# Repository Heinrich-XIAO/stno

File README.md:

# stno

stno is a one-handed steno keyboard with joysticks for my thumb. I wanted to make stno because I became obsessed with steno, didn't have an n-key roll over keyboard and i didnt want to keep arpegiating, and i wanted a one-handed keyboard like my other keyboards (all of them were too small for a steno layout). I wanted to use joysticks since i feel like holding two keys with one finger is awkward and wanted to minimize it, especially for the thumb.

## 🟩PCB

## 📐Schematic

## 📏CAD

## 📦BOM

| Name                 | Price (and Currency) | Link/source                                                                                | Notes                                                                                                                                                                                                                   |
|----------------------|----------------------|--------------------------------------------------------------------------------------------|-------------------------------------------------------------------------------------------------------------------------------------------------------------------------------------------------------------------------|
| Springs              | $13.49 CAD           | https://www.aliexpress.com/item/1005006171011050.html                                      | $4.52 after welcome deal                                                                                                                                                                                                |
| TTC Neptune Switches | $27.26 USD           | https://milktooth.com/products/neptune                                                     | $5.09 per pack $11.99 shipping                                                                                                                                                                                          |
| Arduino Nano ESP32   | $29.67 USD           | https://store-usa.arduino.cc/products/nano-esp32                                           |                                                                                                                                                                                                                         |
| Joysticks            | $21.67 CAD           | https://www.amazon.com/PS5-Hall-Effect-Joystick-Replacement-2-Pack/dp/B0DN8T9KJW           | $7.68 shipping + $13.99                                                                                                                                                                                                 |
| Thumbscrews          | $13.99 CAD           | https://www.amazon.ca/MECCANIXITY-Stainless-Thumbscrew-Appliances-Electronic/dp/B0F282TJ7D |                                                                                                                                                                                                                         |
| Nuts and Bolts       | $13.11 CAD           | https://www.amazon.ca/Walfront-Socket-Head-Button-Screws/dp/B0742DDLQ1                     | this is an assortment of screws but its still somehow cheaper than some non-assortements ive found. it also means hackclub won't have to pay for 10 dollars worth of bolts every time i need a different length of bolt |
| Keycaps              | $5.31 CAD            | https://www.aliexpress.com/item/1005008653485944.html                                      | 3 packs of ten $1.36 per pack                                                                                                                                                                                           |
| Heatset Inserts      | $4.79 CAD            | https://www.aliexpress.com/item/1005003582355741.html                                      | m3 4mm $1.39 after welcome deal                                                                                                                                                                                         |
| Hotswap Sockets      | $9.83 CAD            | https://www.aliexpress.com/item/1005003913466247.html                                      | $1.39 after welcome deal                                                                                                                                                                                                |
| PCB                  | $31.82 USD           | JLCPCB                                                                                     |                                                                                                                                                                                                                         

Total: $145.99 USD

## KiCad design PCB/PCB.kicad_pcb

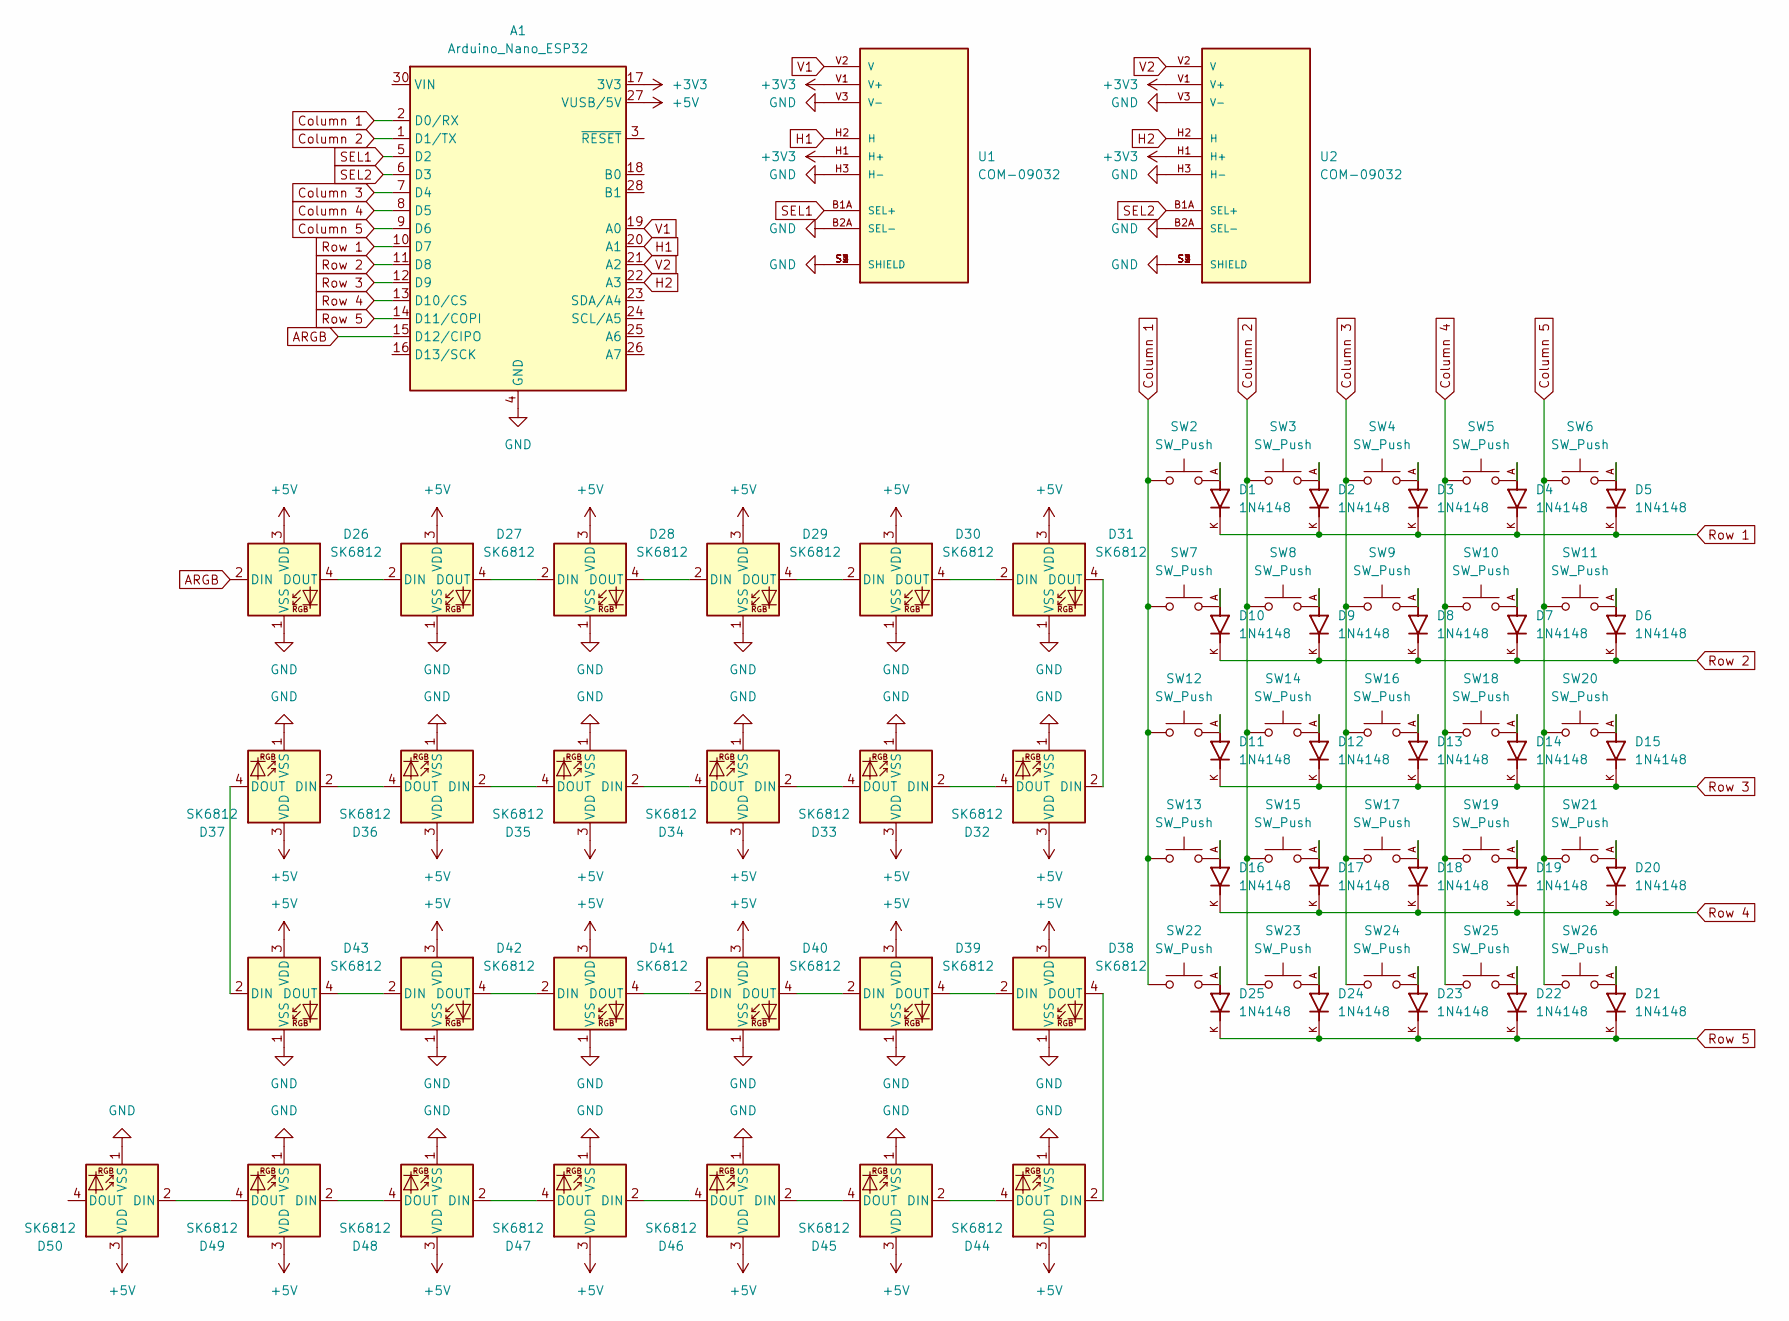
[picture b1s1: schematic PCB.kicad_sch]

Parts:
A1: Arduino_Nano_ESP32; Arduino_Nano
D1, D2, D3, D4, D5, D6, D7, D8, D9, D10, D11, D12, D13, D14, D15, D16, D17, D18, D19, D20, D21, D22, D23, D24, D25: 1N4148; DIOAD753W49L380D172B; PARTREV 5
D26, D27, D28, D29, D30, D31, D32, D33, D34, D35, D36, D37, D38, D39, D40, D41, D42, D43, D44, D45, D46, D47, D48, D49, D50: SK6812; LED_SK6812_PLCC4_5.0x5.0mm_P3.2mm
SW2, SW3, SW4, SW5, SW6, SW7, SW8, SW9, SW10, SW11, SW12, SW13, SW14, SW15, SW16, SW17, SW18, SW19, SW20, SW21, SW22, SW23, SW24, SW25, SW26: SW_Push; hotswap
U1, U2: COM-09032; PS4_joystick; PARTREV N/A

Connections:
+3V3: A1.17 (3V3), U1.H1 (H+), U1.V1 (V+), U2.H1 (H+), U2.V1 (V+)
+5V: A1.27 (VUSB/5V), D26.3 (VDD), D27.3 (VDD), D28.3 (VDD), D29.3 (VDD), D30.3 (VDD), D31.3 (VDD), D32.3 (VDD), D33.3 (VDD), D34.3 (VDD), D35.3 (VDD), D36.3 (VDD), D37.3 (VDD), D38.3 (VDD), D39.3 (VDD), D40.3 (VDD), D41.3 (VDD), D42.3 (VDD), D43.3 (VDD), D44.3 (VDD), D45.3 (VDD), D46.3 (VDD), D47.3 (VDD), D48.3 (VDD), D49.3 (VDD), D50.3 (VDD)
ARGB: A1.15 (D12/CIPO), D26.2 (DIN)
Column 1: A1.2 (D0/RX), SW2.1, SW7.1, SW12.1, SW13.1, SW22.1
Column 2: A1.1 (D1/TX), SW3.1, SW8.1, SW14.1, SW15.1, SW23.1
Column 3: A1.7 (D4), SW4.1, SW9.1, SW16.1, SW17.1, SW24.1
Column 4: A1.8 (D5), SW5.1, SW10.1, SW18.1, SW19.1, SW25.1
Column 5: A1.9 (D6), SW6.1, SW11.1, SW20.1, SW21.1, SW26.1
GND: A1.4 (GND), A1.29 (GND), D26.1 (VSS), D27.1 (VSS), D28.1 (VSS), D29.1 (VSS), D30.1 (VSS), D31.1 (VSS), D32.1 (VSS), D33.1 (VSS), D34.1 (VSS), D35.1 (VSS), D36.1 (VSS), D37.1 (VSS), D38.1 (VSS), D39.1 (VSS), D40.1 (VSS), D41.1 (VSS), D42.1 (VSS), D43.1 (VSS), D44.1 (VSS), D45.1 (VSS), D46.1 (VSS), D47.1 (VSS), D48.1 (VSS), D49.1 (VSS), D50.1 (VSS), U1.B2A (SEL-), U1.H3 (H-), U1.S1 (SHIELD), U1.S2 (SHIELD), U1.S3 (SHIELD), U1.S4 (SHIELD), U1.V3 (V-), U2.B2A (SEL-), U2.H3 (H-), U2.S1 (SHIELD), U2.S2 (SHIELD), U2.S3 (SHIELD), U2.S4 (SHIELD), U2.V3 (V-)
H1: A1.20 (A1), U1.H2 (H)
H2: A1.22 (A3), U2.H2 (H)
unnamed: D1.A, SW2.2
unnamed: D2.A, SW3.2
unnamed: D3.A, SW4.2
unnamed: D4.A, SW5.2
unnamed: D5.A, SW6.2
unnamed: D6.A, SW11.2
unnamed: D7.A, SW10.2
unnamed: D8.A, SW9.2
unnamed: D9.A, SW8.2
unnamed: D10.A, SW7.2
unnamed: D11.A, SW12.2
unnamed: D12.A, SW14.2
unnamed: D13.A, SW16.2
unnamed: D14.A, SW18.2
unnamed: D15.A, SW20.2
unnamed: D16.A, SW13.2
unnamed: D17.A, SW15.2
unnamed: D18.A, SW17.2
unnamed: D19.A, SW19.2
unnamed: D20.A, SW21.2
unnamed: D21.A, SW26.2
unnamed: D22.A, SW25.2
unnamed: D23.A, SW24.2
unnamed: D24.A, SW23.2
unnamed: D25.A, SW22.2
unnamed: D26.4 (DOUT), D27.2 (DIN)
unnamed: D27.4 (DOUT), D28.2 (DIN)
unnamed: D28.4 (DOUT), D29.2 (DIN)
unnamed: D29.4 (DOUT), D30.2 (DIN)
unnamed: D30.4 (DOUT), D31.2 (DIN)
unnamed: D31.4 (DOUT), D32.2 (DIN)
unnamed: D32.4 (DOUT), D33.2 (DIN)
unnamed: D33.4 (DOUT), D34.2 (DIN)
unnamed: D34.4 (DOUT), D35.2 (DIN)
unnamed: D35.4 (DOUT), D36.2 (DIN)
unnamed: D36.4 (DOUT), D37.2 (DIN)
unnamed: D37.4 (DOUT), D43.2 (DIN)
unnamed: D38.2 (DIN), D39.4 (DOUT)
unnamed: D38.4 (DOUT), D44.2 (DIN)
unnamed: D39.2 (DIN), D40.4 (DOUT)
unnamed: D40.2 (DIN), D41.4 (DOUT)
unnamed: D41.2 (DIN), D42.4 (DOUT)
unnamed: D42.2 (DIN), D43.4 (DOUT)
unnamed: D44.4 (DOUT), D45.2 (DIN)
unnamed: D45.4 (DOUT), D46.2 (DIN)
unnamed: D46.4 (DOUT), D47.2 (DIN)
unnamed: D47.4 (DOUT), D48.2 (DIN)
unnamed: D48.4 (DOUT), D49.2 (DIN)
unnamed: D49.4 (DOUT), D50.2 (DIN)
Row 1: A1.10 (D7), D1.K, D2.K, D3.K, D4.K, D5.K
Row 2: A1.11 (D8), D6.K, D7.K, D8.K, D9.K, D10.K
Row 3: A1.12 (D9), D11.K, D12.K, D13.K, D14.K, D15.K
Row 4: A1.13 (D10/CS), D16.K, D17.K, D18.K, D19.K, D20.K
Row 5: A1.14 (D11/COPI), D21.K, D22.K, D23.K, D24.K, D25.K
SEL1: A1.5 (D2), U1.B1A (SEL+)
SEL2: A1.6 (D3), U2.B1A (SEL+)
V1: A1.19 (A0), U1.V2 (V)
V2: A1.21 (A2), U2.V2 (V)

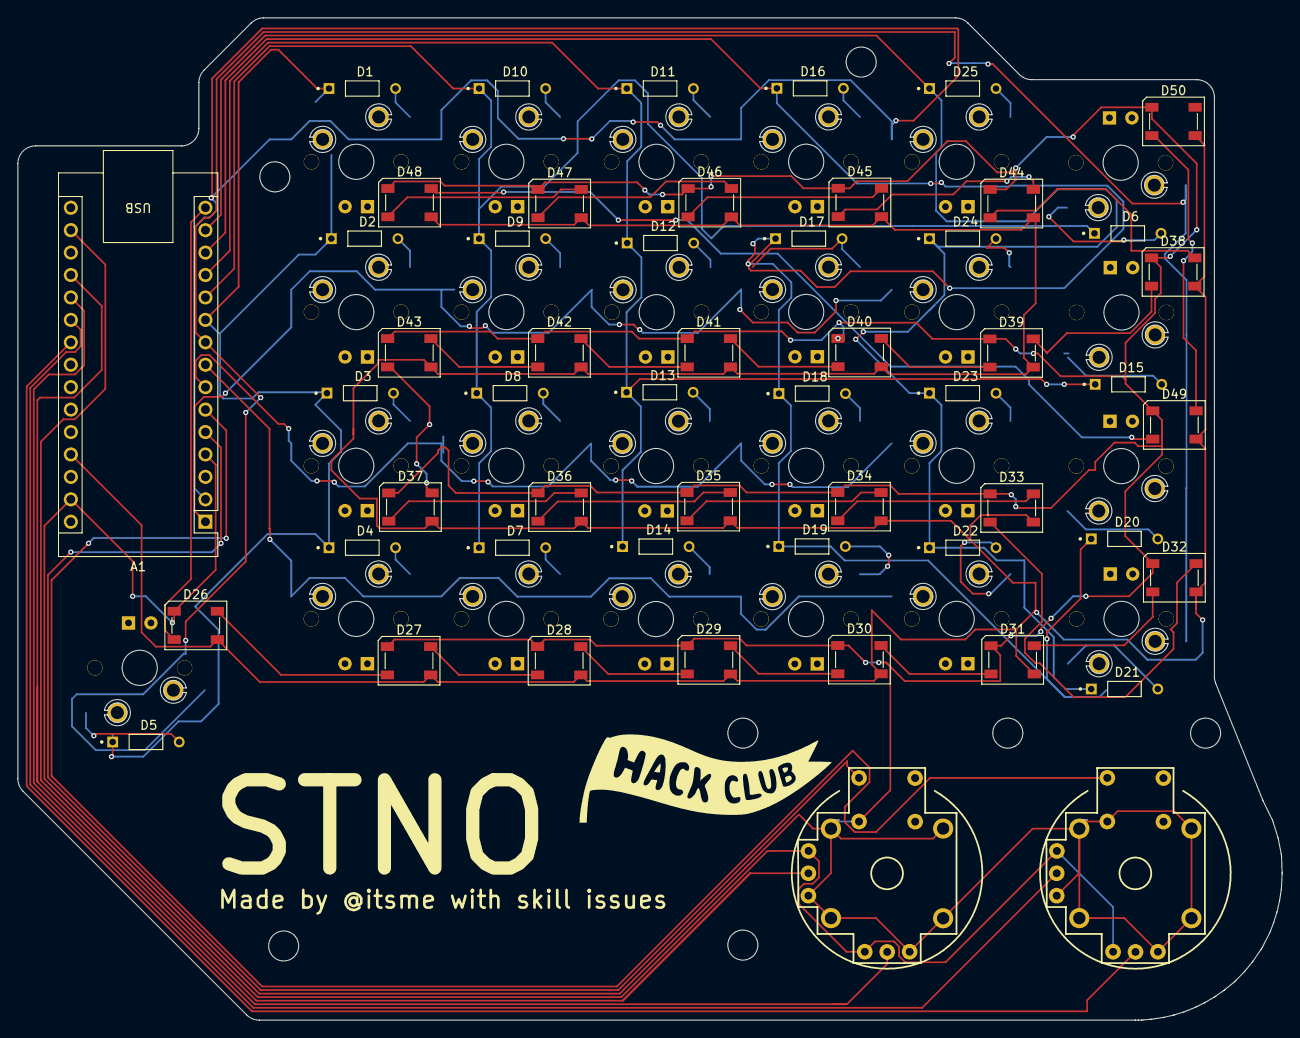
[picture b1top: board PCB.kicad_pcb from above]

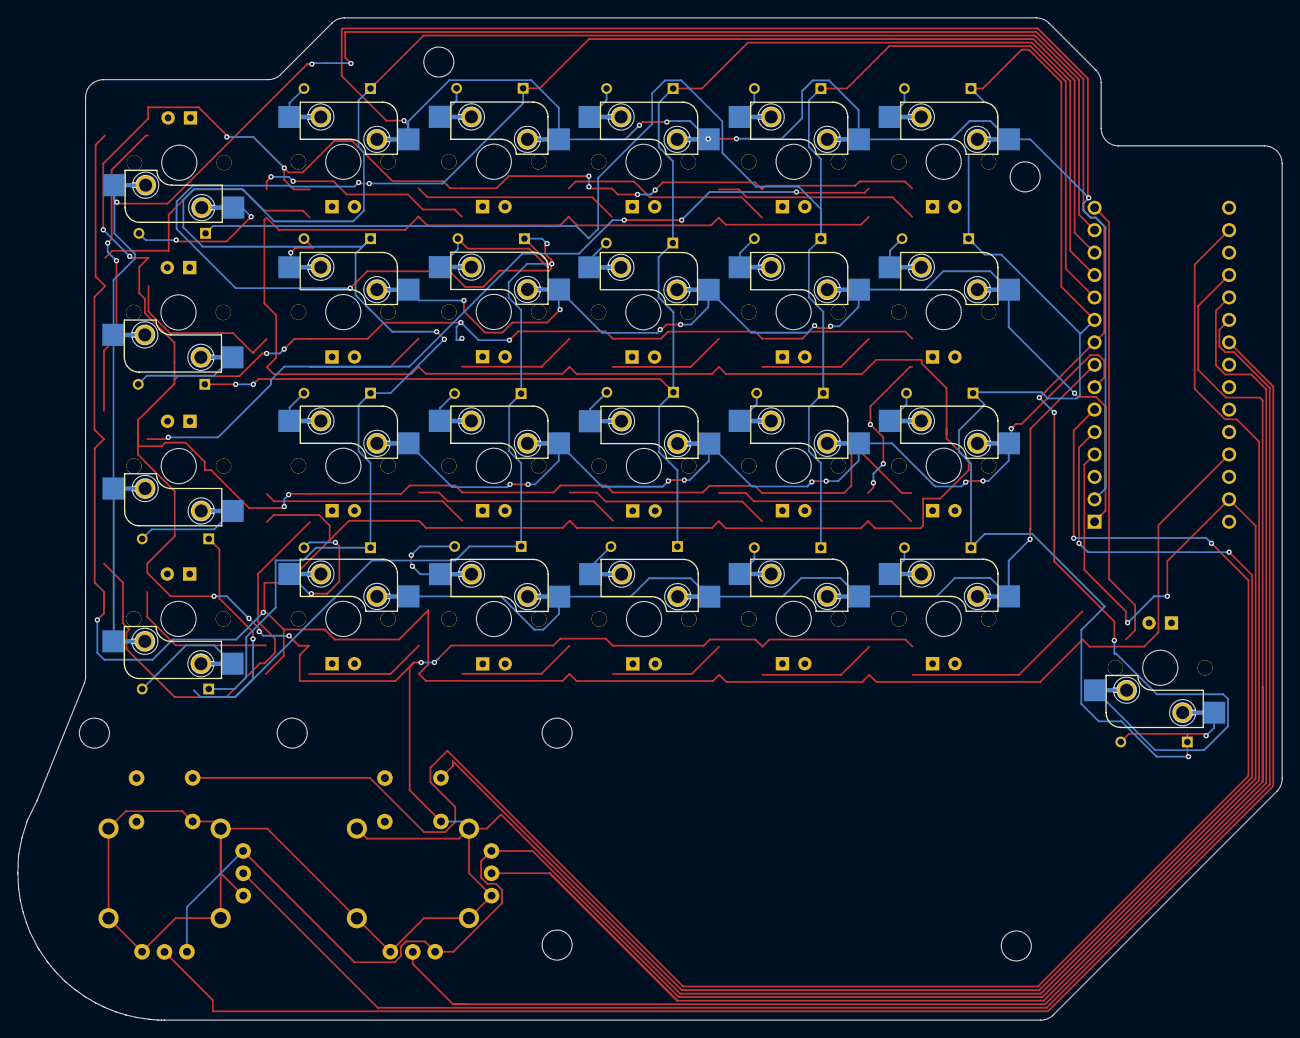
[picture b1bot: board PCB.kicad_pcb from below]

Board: 2 copper layers, 143.1 x 113.5 mm, 78 parts (25 on the bottom side), 69 nets.

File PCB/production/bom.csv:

Designator,Footprint,Quantity,Value,LCSC Part #
A1,Arduino_Nano,1,Arduino_Nano_ESP32,
"D1, D10, D11, D12, D13, D14, D15, D16, D17, D18, D19, D2, D20, D21, D22, D23, D24, D25, D3, D4, D5, D6, D7, D8, D9",DIOAD753W49L380D172B,25,1N4148,
"D26, D27, D28, D29, D30, D31, D32, D33, D34, D35, D36, D37, D38, D39, D40, D41, D42, D43, D44, D45, D46, D47, D48, D49, D50",LED_SK6812_PLCC4_5.0x5.0mm_P3.2mm,25,SK6812,
"SW10, SW11, SW12, SW13, SW14, SW15, SW16, SW17, SW18, SW19, SW2, SW20, SW21, SW22, SW23, SW24, SW25, SW26, SW3, SW4, SW5, SW6, SW7, SW8, SW9",hotswap,25,SW_Push,
"U1, U2",PS4_joystick,2,COM-09032,

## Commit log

2025-06-21 schemaitc done currently working on pcb
2025-06-22 made pcb
2025-06-22 backjournaled (i really need to remember to journal in the moment
2025-06-22 ignore ds store
2025-06-22 get rid of lock files
2025-06-22 remove unnecessary files
2025-06-22 fix edge cuts layer
2025-06-22 move text to the right layer and fix the edge cuts
2025-06-23 whoops, i used the radius instead of the diametre and the circles were twice as big
2025-06-24 Update JOURNAL.md for yesterday
    github is horrible on Mobile
2025-06-24 rant about school chromebooks
2025-06-24 fix the joystick footprint
2025-06-27 put all the hotswap switches on the right side
2025-06-27 journla update for yesterday
2025-06-27 whoops, it was 2 hr 30m not 5hr
2025-06-27 hotswap switches fixed
2025-06-28 ajouter des empreintes pour les touches, les diodes, et le microcontrôleur
2025-06-28 journal update for today and tw days ago
2025-06-30 idk what i updated
2025-06-30 added a bomb
2025-06-30 pcb price added
2025-06-30 formatting also total
2025-06-30 migh've mess up some math
2025-06-30 yup, my math was wrong last time
2025-07-02 firmware done
2025-07-02 quickly made journal entry
2025-07-02 cad files
2025-07-02 i cant add
2025-07-03 Update README.md
    why did they chang etheir prices
2025-07-19 new screenshot
2025-07-19 stuff
2025-07-19 bom b in table
2025-07-19 prod folder
2025-07-20 Update bom.csv to fix formatting
2025-07-20 Update bom.csv to fix formatting (again)
2025-07-20 Update bom.csv i think i finally fixed the formatting
2025-07-20 Update bom.csv i fucking hate csv
2025-07-20 Update bom.csv wtf
2025-07-20 Update README.md to use shit from bom.csv instead of crappy bom converted from list by chatccp (deepseek)
